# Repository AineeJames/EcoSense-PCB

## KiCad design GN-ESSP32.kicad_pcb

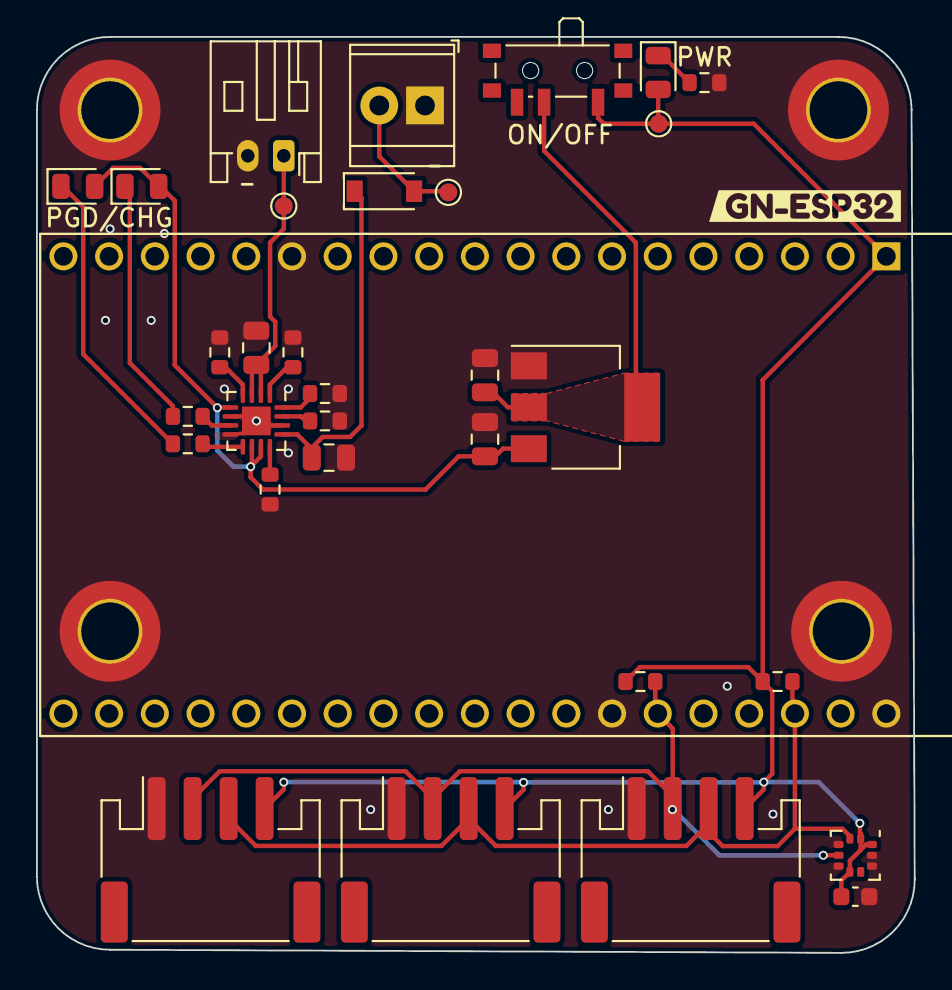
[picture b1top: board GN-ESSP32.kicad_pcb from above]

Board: 2 copper layers, 48.8 x 50.9 mm, 37 parts (0 on the bottom side), 19 nets.

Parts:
C1: 1uF; C_0805_2012Metric
C3: 4.7uF; C_0805_2012Metric
C4: 10uF; C_0805_2012Metric
C5: 22uF; C_0805_2012Metric
C6: 0.1uF; C_0603_1608Metric
D1: D; D_SOD-123
D2: PG; D_0805_2012Metric
D3: CHG; D_0805_2012Metric
D4: PWR; D_0805_2012Metric
H1, H2, H3, H4: GND; MountingHole_3.2mm_M3_DIN965_Pad_TopBottom
J1, J2, J3: I2C; JST_PH_S4B-PH-SM4-TB_1x04-1MP_P2.00mm_Horizontal
J4: SOLAR; TerminalBlock_TE_282834-2_1x02_P2.54mm_Horizontal
J5: BATT; JST_PH_S2B-PH-K_1x02_P2.00mm_Horizontal
R1, R2: 4.7k; R_0603_1608Metric
R3, R4, R5: 1k; R_0603_1608Metric
R6, R7, R8, R9, R10: 10k; R_0603_1608Metric
SW1: SW_SPDT; SW_SPDT_PCM12
TP1: SOLAR_TP; TestPoint_Pad_D1.0mm
TP2: LIPO_TP; TestPoint_Pad_D1.0mm
TP3: 3V3_TP; TestPoint_Pad_D1.0mm
U1: LPS25HB; ST_HLGA-10_2.5x2.5mm_P0.6mm_LayoutBorder3x2y
U2: BQ24074RGT; VQFN-16-1EP_3x3mm_P0.5mm_EP1.6x1.6mm
U3: AZ1117-3.3; SOT-223-3_TabPin2
U4: ESP32-DEVKITC-32D; MODULE_ESP32-DEVKITC-32D
kibuzzard-63D1EA0B: G***; kibuzzard-63D1EA0B

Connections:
+3.3V: C6.1, D4.2 (A), J1.4, J2.4, J3.4, R1.1, R2.1, SW1.1 (A), TP3.1, U1.1 (VDDio), U1.6 (~CS), U1.10 (VDD), U4.1 (3V3)
GND: C1.2, C3.2, C4.2, C5.2, C6.2, H1.1, H2.1, H3.1, H4.1, J1.1, J2.1, J3.1, J4.1, J5.2, R3.2, R4.2, R5.2, R6.2, R9.2, R10.1, U1.3 (GND), U1.5 (SA0/MISO), U1.8 (GND), U1.9 (GND), U2.6 (EN1), U2.8 (VSS), U2.14 (TMR), U2.17 (VSS), U3.1 (GND), U4.14 (GND1), U4.20 (GND3), U4.26 (GND2)
unnamed: C1.1, D1.1 (K), U2.13 (IN)
unnamed: C3.1, J5.1, TP2.1, U2.2 (BAT), U2.3 (BAT)
unnamed: C5.1, SW1.2 (B), U3.2 (VO)
unnamed: D1.2 (A), J4.2, TP1.1
unnamed: D2.1 (K), R7.1
unnamed: D3.1 (K), R8.1
unnamed: D4.1 (K), R10.2
unnamed: R3.1, U2.12 (ILIM)
unnamed: R4.1, U2.16 (ISET)
unnamed: R5.1, U2.15 (ITERM)
unnamed: R6.1, U2.4 (~CE)
unnamed: R7.2, U2.9 (~CHG)
unnamed: R8.2, U2.7 (~PGOOD)
unnamed: R9.1, U2.1 (TS)
OUT: C4.1, D2.2 (A), D3.2 (A), U2.5 (EN2), U2.10 (OUT), U2.11 (OUT), U3.3 (VI)
SCL: J1.3, J2.3, J3.3, R2.2, U1.2 (SCL/SCLK), U4.22 (IO22)
SDA: J1.2, J2.2, J3.2, R1.2, U1.4 (SDA/MOSI), U4.25 (IO21)

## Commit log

2023-04-26 init
